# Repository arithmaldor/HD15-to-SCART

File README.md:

# Copyright and Disclaimer
Copyright: Jacob Proctor

This documentation describes Open Hardware and is licensed under the
CERN OHL v. 1.2.

You may redistribute and modify this documentation under the terms of the
CERN OHL v.1.2. (http://ohwr.org/cernohl). This documentation is distributed
WITHOUT ANY EXPRESS OR IMPLIED WARRANTY, INCLUDING OF
MERCHANTABILITY, SATISFACTORY QUALITY AND FITNESS FOR A
PARTICULAR PURPOSE. Please see the CERN OHL v.1.2 for applicable
conditions

# VGA to SCART
This is a passive adapter that simply connects the RGB and sync pins from a VGA connector and the right and left audio pins from a 3.5mm jack to the corresponding pins on
a male SCART connector. It is unidirectional and cannot be used for VGA output from a SCART device. It does not convert RGBHV to RGBS or 31khz to 15khz or anything fancy like that.
# Uses
The main purpose of this board for me is to replace SCART cables with VGA cables. Using this adapter you can run a VGA cable from a breakout adapter to a gscartsw for example without
having to worry about making your own cables or having custom ones made. I'm sure that other uses can be found.
# BOM
There are only 3 parts so I thought I would just list them here instead of making a full BOM. Listed are digikey links but the parts are pretty common and it should be possible to substitute others, just compare datasheets for the footprints.
VGA Connector: https://www.digikey.com/product-detail/en/amphenol-icc-fci/ICD15S13E6GV00LF/609-2802-ND/1090326
Headphone Jack: https://www.digikey.com/product-detail/en/cui-inc/SJ1-3533NG/CP1-3533NG-ND/738701
SCART Connector: Any will do, console5.com has new ones and reclaimed ones.
New: https://console5.com/store/scart-plug-21-pin-male-cable-connector.html
Reclaimed: https://console5.com/store/reclaimed-scart-jp21-plug-21-pin-male-cable-connector.html
# Assembly
Use the photos for reference. Pin 20 of the SCART connector (the point) goes towards the left when looking at the top of the board. You can also solder a wire or component leg between the shield and the spare ground pin on the board.

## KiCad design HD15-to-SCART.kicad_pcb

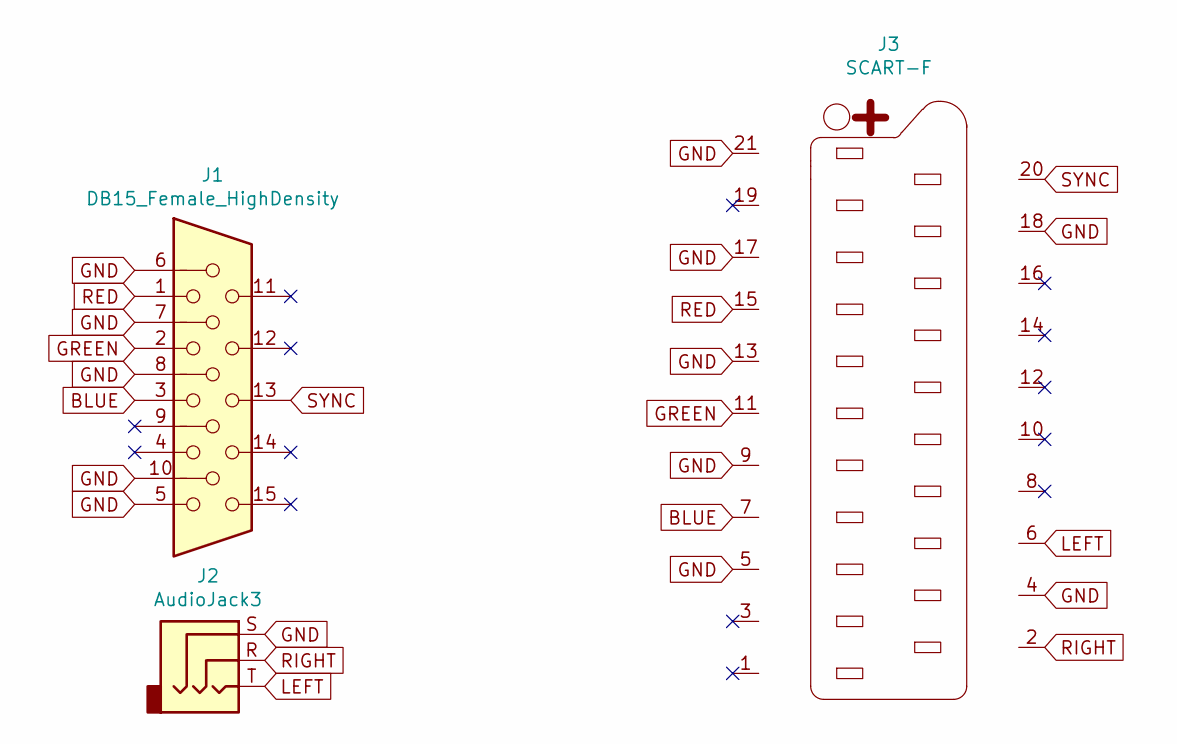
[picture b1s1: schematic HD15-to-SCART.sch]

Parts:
J1: DB15_Female_HighDensity; VGA
J2: AudioJack3; Tall_Skinny_Headphone_Universal_CUI_SJ1-353XNX
J3: SCART-F; MALE_SCART

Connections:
BLUE: J1.3, J3.7
GND: J1.0, J1.5, J1.6, J1.7, J1.8, J1.10, J2.S, J3.4, J3.5, J3.9, J3.13, J3.17, J3.18, J3.21
GREEN: J1.2, J3.11
LEFT: J2.T, J3.6
RED: J1.1, J3.15
RIGHT: J2.R, J3.2
SYNC: J1.13, J3.20

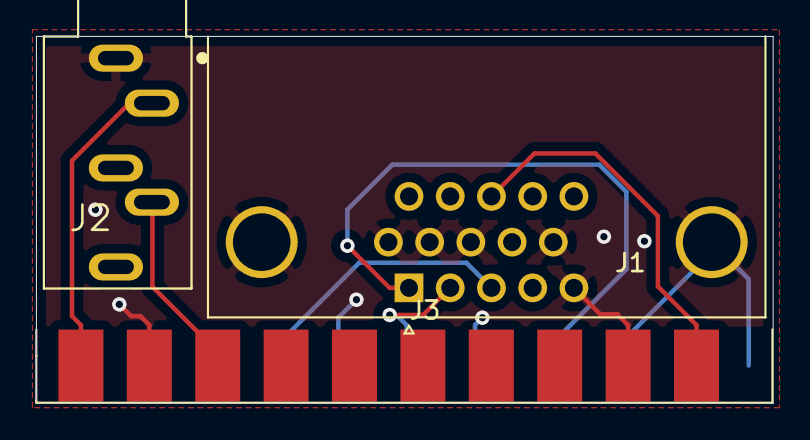
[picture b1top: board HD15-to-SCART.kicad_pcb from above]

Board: 2 copper layers, 40.9 x 20.4 mm, 3 parts (0 on the bottom side), 7 nets.

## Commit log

2019-06-12 Initial Commit
    Created repository, started brainstorming with schematic
2019-06-17 Updated list of parts to try
2019-06-20 Finished schematic and designed pcb
2019-06-25 Create gerber zip
2019-07-29 fixed headphone footprint, regenerated gerbers
2019-08-02 Finishing Touches
